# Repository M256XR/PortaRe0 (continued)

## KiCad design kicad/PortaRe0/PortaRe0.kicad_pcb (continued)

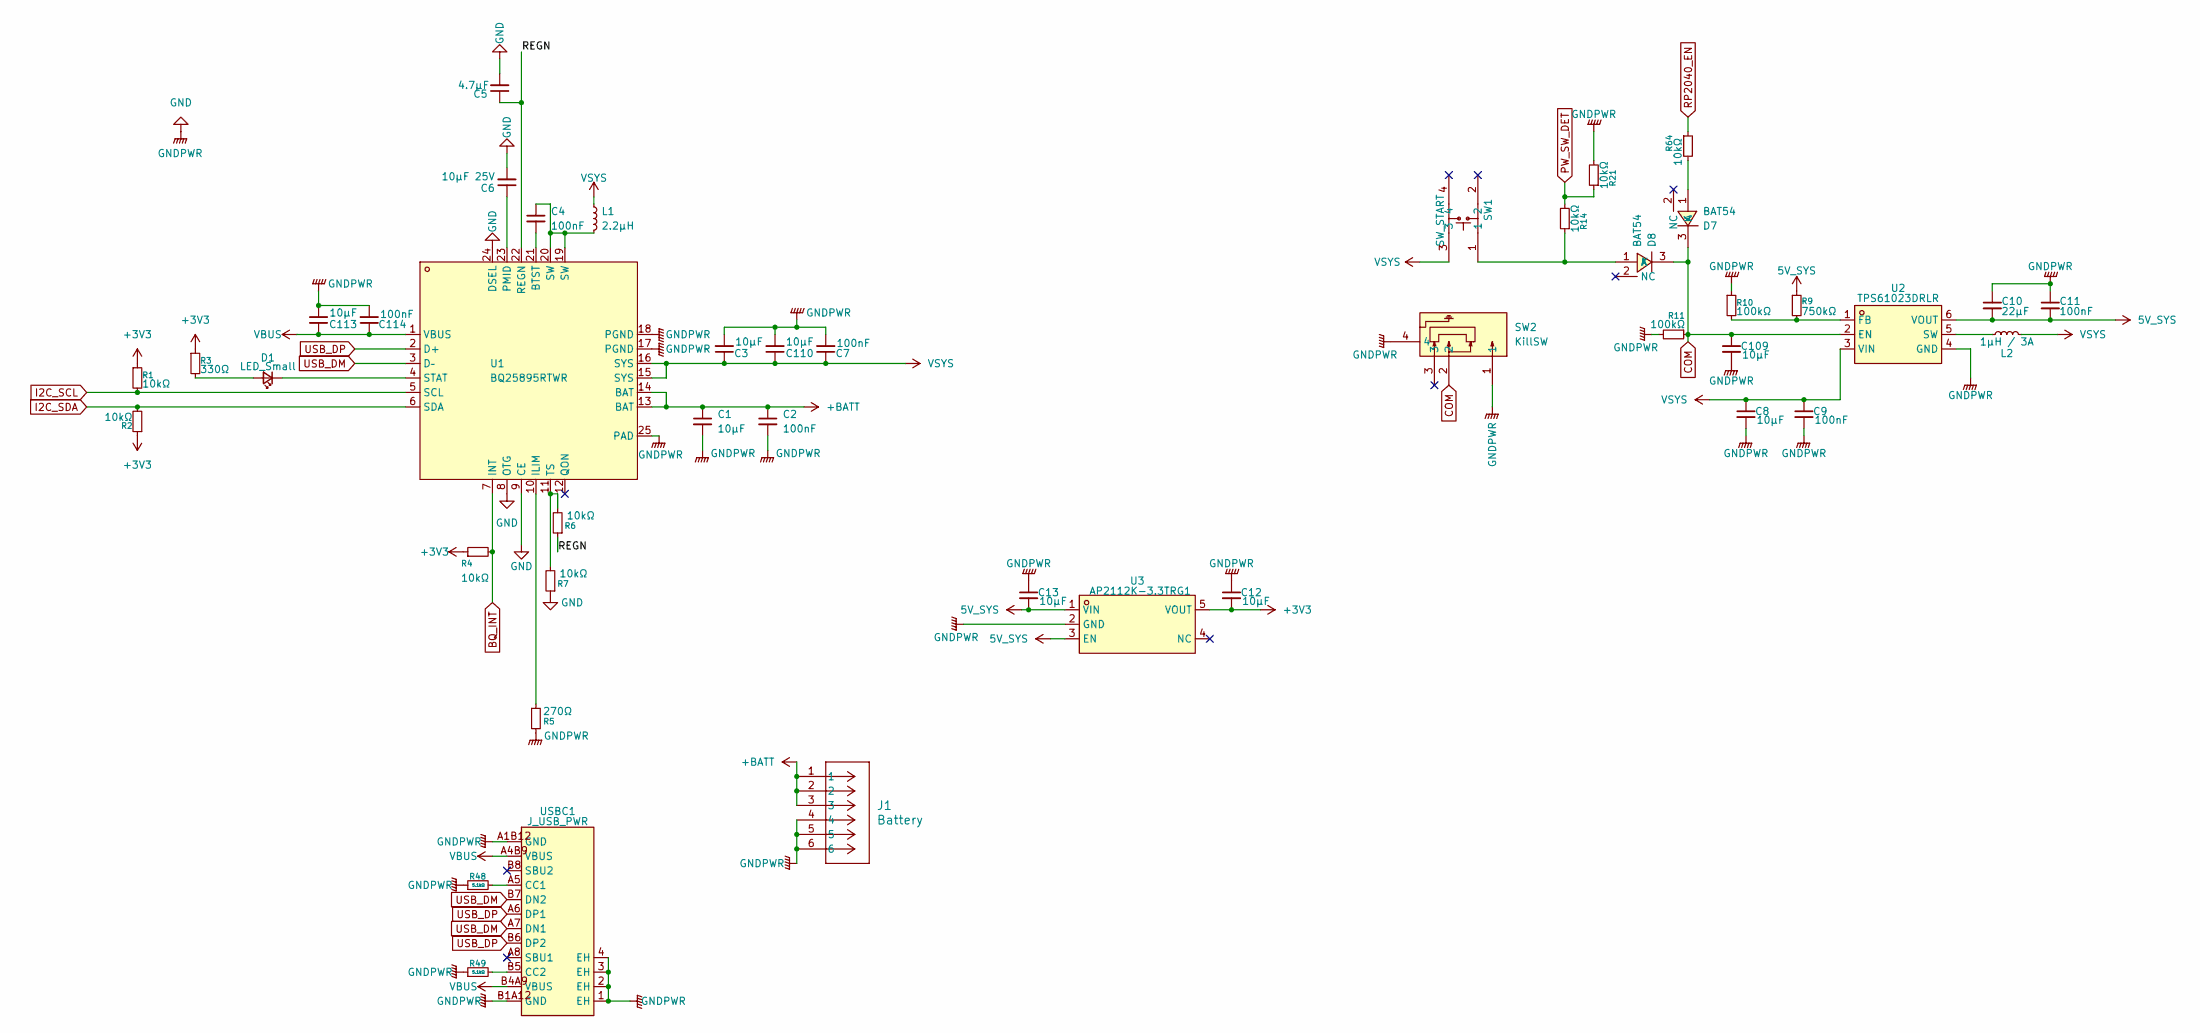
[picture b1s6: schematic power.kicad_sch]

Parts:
C1, C3, C8, C13, C109, C110, C113: 10μF; C_0603_1608Metric
C2, C4, C7, C9, C11, C114: 100nF; C_0402_1005Metric
C5: 4.7μF; C_0402_1005Metric
C6: 10μF 25V; C_0603_1608Metric
C10: 22μF; C_0603_1608Metric
C12: 10μF; C_0402_1005Metric
D1: LED_Small; LED_0603_1608Metric
D7, D8: BAT54; SOT-23-3_L2.9-W1.4-P1.90-LS2.6-BR; LCSC Part C466635
J1: Battery; CONN_BM06B-ACHFKS-GACN-ETF_JST
L1: 2.2μH; IND-SMD_L4.4-W4.2
L2: 1µH / 3A; IND-SMD_L3.2-W2.5_CKST322512-2.2UH
R1, R2, R4, R6, R7, R14, R21, R64: 10kΩ; R_0402_1005Metric
R3: 330Ω; R_0402_1005Metric
R5: 270Ω; R_0603_1608Metric
R9: 750kΩ; R_0603_1608Metric
R10, R11: 100kΩ; R_0402_1005Metric
R48, R49: 5.1kΩ; R_0402_1005Metric
SW1: SW_START; KEY-SMD_4P-SKSCLXX010; LCSC Part C115361
SW2: KillSW; SW-TH_MSK12C02; LCSC Part C431540
U1: BQ25895RTWR; QFN-24_L4.0-W4.0-P0.50-TL-EP2.7; LCSC Part C80200
U2: TPS61023DRLR; SOT-563_L1.6-W1.2-P0.50-LS1.6-BR; LCSC Part C919459
U3: AP2112K-3.3TRG1; SOT-25-5_L2.9-W1.6-P0.95-LS2.8-BL; LCSC Part C51118
USBC1: J_USB_PWR; USB-C_SMD-TYPE-C-31-M-12_1; LCSC Part C165948

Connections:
5V_SYS: C10.2, C11.2, C13.2, R9.1, U2.6 (VOUT), U3.1 (VIN), U3.3 (EN); also elsewhere on the board
+3V3: C12.2, R1.1, R2.1, R3.1, R4.1, U3.5 (VOUT); also elsewhere on the board
+BATT: C1.1, C2.1, J1.1, J1.2, J1.3, U1.13 (BAT), U1.14 (BAT)
/power/REGN: C5.1, R6.1, U1.22 (REGN)
BQ_INT: R4.2, U1.7 (INT); also elsewhere on the board
COM: C109.1, D7.3 (K), D8.3 (K), R11.1, SW2.2, U2.2 (EN)
GND: C1.2, C2.2, C3.2, C5.2, C6.2, C7.2, C8.2, C9.2, C10.1, C11.1, C12.1, C13.1, C109.2, C110.2, C113.2, C114.2, J1.4, J1.5, J1.6, R5.2, R7.1, R10.1, R11.2, R21.2, R48.1, R49.1, SW2.1, SW2.4, U1.8 (OTG), U1.9 (CE), U1.17 (PGND), U1.18 (PGND), U1.24 (DSEL), U1.25 (PAD), U2.4 (GND), U3.2 (GND), USBC1.1 (EH), USBC1.2 (EH), USBC1.3 (EH), USBC1.4 (EH), USBC1.A1B12 (GND), USBC1.B1A12 (GND); also elsewhere on the board
I2C_SCL: R1.2, U1.5 (SCL); also elsewhere on the board
I2C_SDA: R2.2, U1.6 (SDA); also elsewhere on the board
unnamed: C4.1, L1.2, U1.19 (SW), U1.20 (SW)
unnamed: D1.2 (A), R3.2
unnamed: D1.1 (K), U1.4 (STAT)
unnamed: D7.1 (A), R64.2
unnamed: D8.1 (A), R14.1, SW1.1
unnamed: C4.2, U1.21 (BTST)
unnamed: R5.1, U1.10 (ILIM)
unnamed: C6.1, U1.23 (PMID)
unnamed: R6.2, R7.2, U1.11 (TS)
unnamed: R9.2, R10.2, U2.1 (FB)
unnamed: L2.1, U2.5 (SW)
unnamed: R48.2, USBC1.A5 (CC1)
unnamed: R49.2, USBC1.B5 (CC2)
PW_SW_DET: R14.2, R21.1; also elsewhere on the board
RP2040_EN: R64.1; also elsewhere on the board
USB_DM: U1.3 (D–), USBC1.A7 (DN1), USBC1.B7 (DN2)
USB_DP: U1.2 (D+), USBC1.A6 (DP1), USBC1.B6 (DP2)
VBUS: C113.1, C114.1, U1.1 (VBUS), USBC1.A4B9 (VBUS), USBC1.B4A9 (VBUS)
VSYS: C3.1, C7.1, C8.1, C9.1, C110.1, L1.1, L2.2, SW1.3, U1.15 (SYS), U1.16 (SYS), U2.3 (VIN); also elsewhere on the board

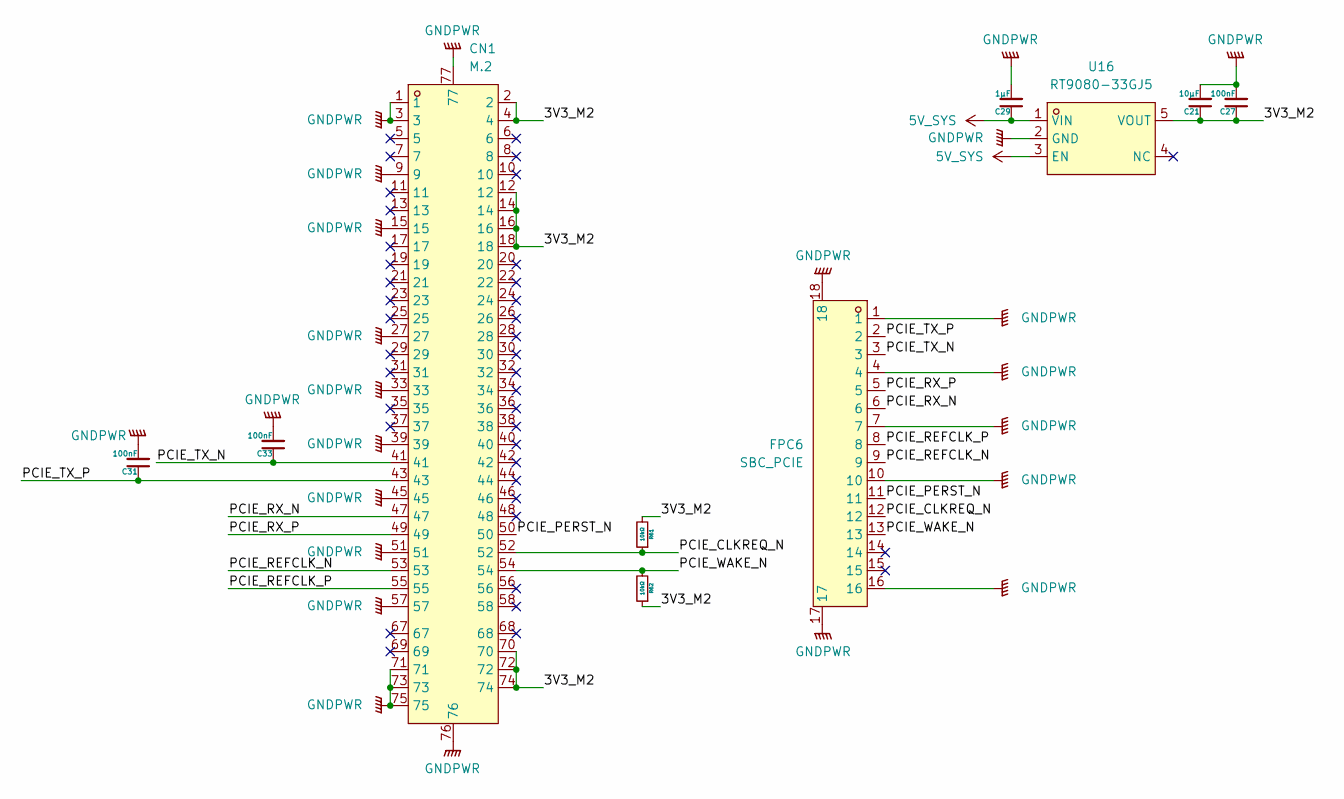
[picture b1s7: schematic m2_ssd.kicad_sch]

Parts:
C21: 10μF; C_0402_1005Metric
C27, C31, C33: 100nF; C_0402_1005Metric
C29: 1μF; C_0402_1005Metric
CN1: M.2; CONN-SMD_67P-P0.50-V_NXSM0-S67XX-XX40; LCSC Part C367029
FPC6: SBC_PCIE; FPC-SMD_16P-P0.50_FPC-05F-16PH20; LCSC Part C2856801
R61, R62: 10kΩ; R_0402_1005Metric
U16: RT9080-33GJ5; TSOT-23-5_L2.9-W1.6-P0.95-LS2.8-BL; LCSC Part C841192

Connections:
5V_SYS: C29.1, U16.1 (VIN), U16.3 (EN); also elsewhere on the board
/m2_ssd/3V3_M2: C21.1, C27.1, CN1.2, CN1.4, CN1.12, CN1.14, CN1.16, CN1.18, CN1.70, CN1.72, CN1.74, R61.2, R62.1, U16.5 (VOUT); also elsewhere on the board
/m2_ssd/PCIE_CLKREQ_N: CN1.52, FPC6.12, R61.1; also elsewhere on the board
/m2_ssd/PCIE_TX_N: C33.1, CN1.41, FPC6.3; also elsewhere on the board
/m2_ssd/PCIE_TX_P: C31.1, CN1.43, FPC6.2; also elsewhere on the board
/m2_ssd/PCIE_WAKE_N: CN1.54, FPC6.13, R62.2; also elsewhere on the board
GND: C21.2, C27.2, C29.2, C31.2, C33.2, CN1.1, CN1.3, CN1.9, CN1.15, CN1.27, CN1.33, CN1.39, CN1.45, CN1.51, CN1.57, CN1.71, CN1.73, CN1.75, CN1.76, CN1.77, FPC6.1, FPC6.4, FPC6.7, FPC6.10, FPC6.16, FPC6.17, FPC6.18, U16.2 (GND); also elsewhere on the board
unnamed: CN1.47, FPC6.6
unnamed: CN1.49, FPC6.5
unnamed: CN1.50, FPC6.11
unnamed: CN1.53, FPC6.9
unnamed: CN1.55, FPC6.8

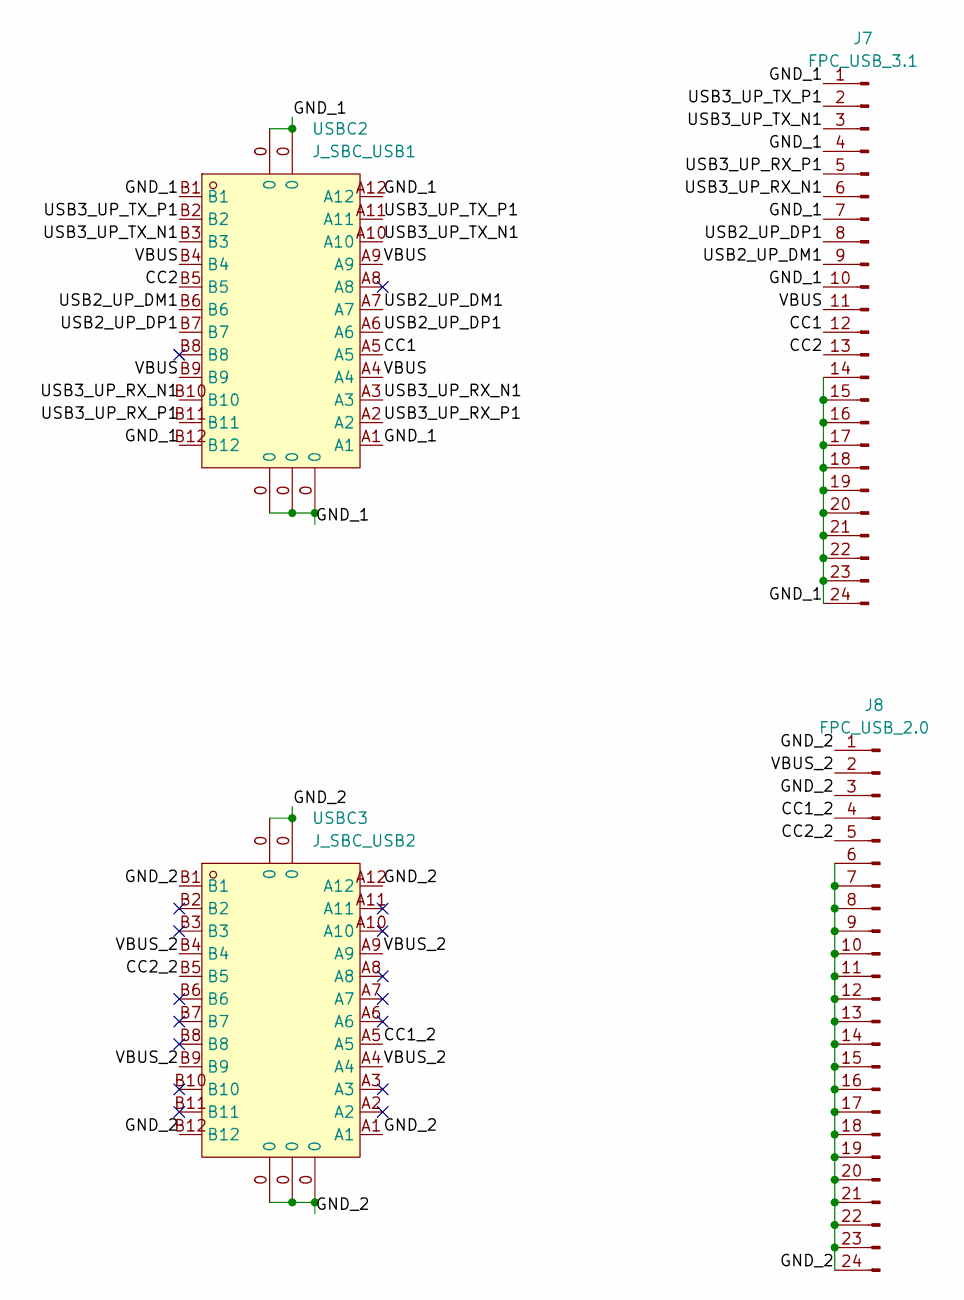
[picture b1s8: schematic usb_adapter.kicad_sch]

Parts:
J7: FPC_USB_3.1
J8: FPC_USB_2.0
USBC2: J_SBC_USB1; USB-C-SMD_TYPE-C-USB-3; LCSC Part C168690
USBC3: J_SBC_USB2; USB-C-SMD_TYPE-C-USB-3; LCSC Part C168690

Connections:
unnamed: J7.1, J7.4, J7.7, J7.10, J7.14, J7.15, J7.16, J7.17, J7.18, J7.19, J7.20, J7.21, J7.22, J7.23, J7.24, USBC2.0, USBC2.A1, USBC2.A12, USBC2.B1, USBC2.B12
unnamed: J7.2, USBC2.A11, USBC2.B2
unnamed: J7.3, USBC2.A10, USBC2.B3
unnamed: J7.5, USBC2.A2, USBC2.B11
unnamed: J7.6, USBC2.A3, USBC2.B10
unnamed: J7.8, USBC2.A6, USBC2.B7
unnamed: J7.9, USBC2.A7, USBC2.B6
unnamed: J7.11, USBC2.A4, USBC2.A9, USBC2.B4, USBC2.B9
unnamed: J7.12, USBC2.A5
unnamed: J7.13, USBC2.B5
unnamed: J8.1, J8.3, J8.6, J8.7, J8.8, J8.9, J8.10, J8.11, J8.12, J8.13, J8.14, J8.15, J8.16, J8.17, J8.18, J8.19, J8.20, J8.21, J8.22, J8.23, J8.24, USBC3.0, USBC3.A1, USBC3.A12, USBC3.B1, USBC3.B12
unnamed: J8.2, USBC3.A4, USBC3.A9, USBC3.B4, USBC3.B9
unnamed: J8.4, USBC3.A5
unnamed: J8.5, USBC3.B5

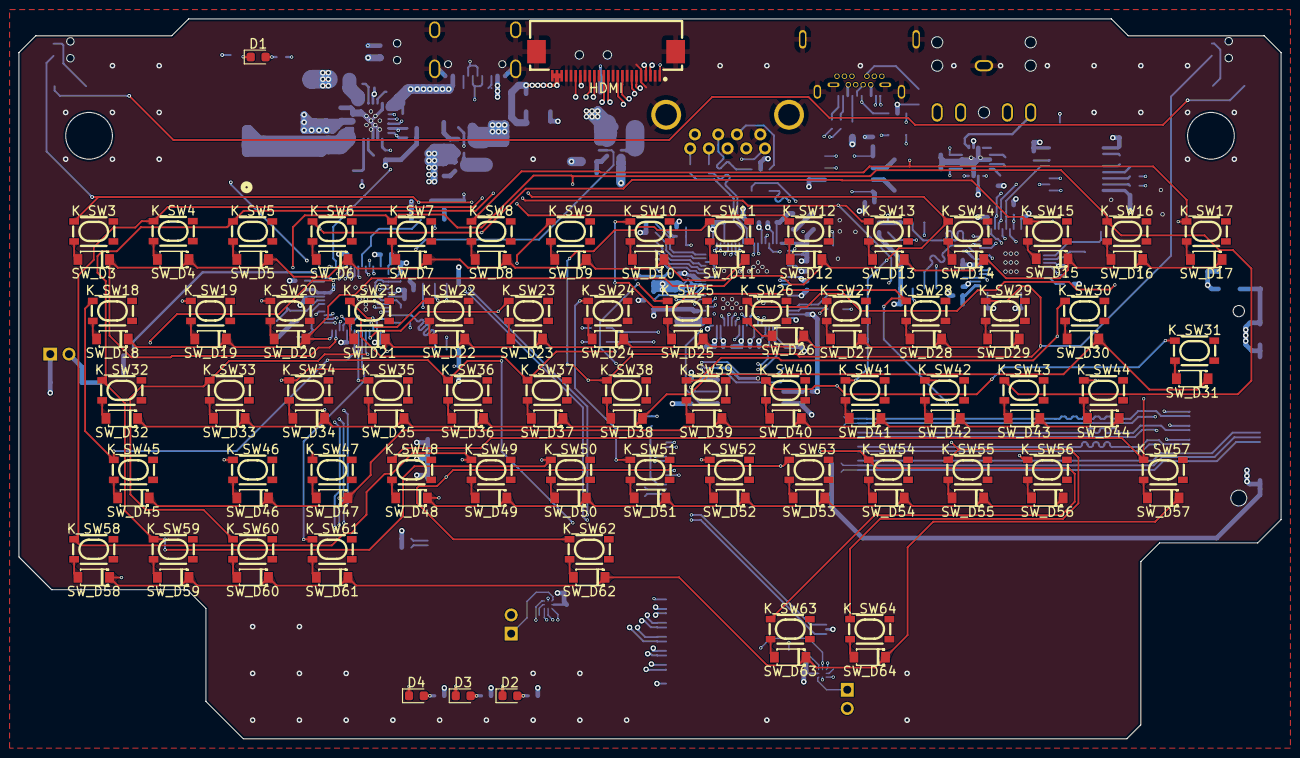
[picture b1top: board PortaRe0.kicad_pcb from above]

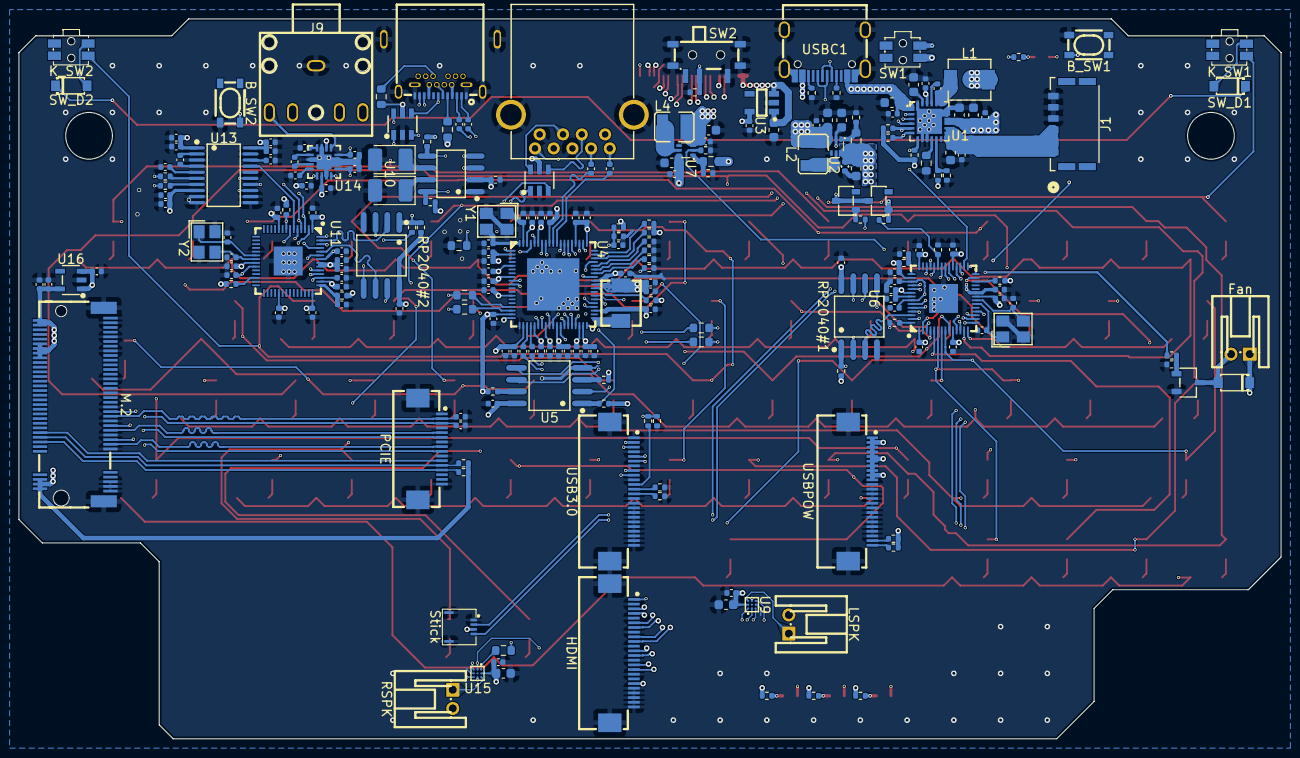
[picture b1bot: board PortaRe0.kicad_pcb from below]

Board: 6 copper layers, 135.0 x 77.0 mm, 357 parts (228 on the bottom side), 266 nets.

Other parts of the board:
Fan: Fan; CONN-TH_S2B-PH-K-S-LF-SN
HDMI: J_HDMI_CTRL; FPC-SMD_24P-P0.50_FPC-05F-24PH20
HDMI#2: J_SBC_HDMI; FPC-SMD_24P-P0.50_FPC-05F-24PH20
LSPK: SPK_L; CONN-TH_S2B-PH-K-S-LF-SN
M.2: M.2; CONN-SMD_67P-P0.50-V_NXSM0-S67XX-XX40
PCIE: SBC_PCIE; FPC-SMD_16P-P0.50_FPC-05F-16PH20
RSPK: SPK_R; CONN-TH_S2B-PH-K-S-LF-SN
Stick: 5034800440; FPC-SMD_5034800400
USB3.0: J_SBC_USB_3.1; FPC-SMD_24P-P0.50_FPC-05F-24PH20
USBPOW: J_SBC_USB_2.0; FPC-SMD_24P-P0.50_FPC-05F-24PH20

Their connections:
5V_SYS: Fan.1, HDMI.18, HDMI.22, HDMI.23, HDMI.24, USBPOW.1, USBPOW.2, USBPOW.3, USBPOW.4, USBPOW.5, USBPOW.6, USBPOW.7, USBPOW.8, USBPOW.9, USBPOW.10; also elsewhere on the board
+3V3: Stick.3; also elsewhere on the board
/Connectors/HDMI_CEC: HDMI.19, HDMI#2.19
/Connectors/HDMI_CLKN: HDMI.13, HDMI#2.13
/Connectors/HDMI_CLKP: HDMI.12, HDMI#2.12
/Connectors/HDMI_D0N: HDMI.10, HDMI#2.10
/Connectors/HDMI_D0P: HDMI.9, HDMI#2.9
/Connectors/HDMI_D1N: HDMI.7, HDMI#2.7
/Connectors/HDMI_D1P: HDMI.6, HDMI#2.6
/Connectors/HDMI_D2N: HDMI.4, HDMI#2.4
/Connectors/HDMI_D2P: HDMI.3, HDMI#2.3
/Connectors/HDMI_HPD: HDMI.1, HDMI#2.1
/Connectors/HDMI_SCL: HDMI.15, HDMI#2.15
/Connectors/HDMI_SDA: HDMI.16, HDMI#2.16
/audio/SPK_L+: LSPK.1; also elsewhere on the board
/audio/SPK_L-: LSPK.2; also elsewhere on the board
/audio/SPK_R+: RSPK.1; also elsewhere on the board
/audio/SPK_R-: RSPK.2; also elsewhere on the board
/m2_ssd/3V3_M2: M.2.2, M.2.4, M.2.12, M.2.14, M.2.16, M.2.18, M.2.70, M.2.72, M.2.74; also elsewhere on the board
/m2_ssd/PCIE_CLKREQ_N: M.2.52, PCIE.12; also elsewhere on the board
/m2_ssd/PCIE_PERST_N: M.2.50, PCIE.11
/m2_ssd/PCIE_REFCLK_N: M.2.53, PCIE.9
/m2_ssd/PCIE_REFCLK_P: M.2.55, PCIE.8
/m2_ssd/PCIE_RX_N: M.2.47, PCIE.6
/m2_ssd/PCIE_RX_P: M.2.49, PCIE.5
/m2_ssd/PCIE_TX_N: M.2.41, PCIE.3; also elsewhere on the board
/m2_ssd/PCIE_TX_P: M.2.43, PCIE.2; also elsewhere on the board
/m2_ssd/PCIE_WAKE_N: M.2.54, PCIE.13; also elsewhere on the board
GND: HDMI.2, HDMI.5, HDMI.8, HDMI.11, HDMI.14, HDMI.17, HDMI.20, HDMI.21, HDMI.25, HDMI.26, HDMI#2.2, HDMI#2.5, HDMI#2.8, HDMI#2.11, HDMI#2.14, HDMI#2.17, HDMI#2.20, HDMI#2.21, HDMI#2.22, HDMI#2.23, HDMI#2.24, HDMI#2.25, HDMI#2.26, M.2.1, M.2.3, M.2.9, M.2.15, M.2.27, M.2.33, M.2.39, M.2.45, M.2.51, M.2.57, M.2.71, M.2.73, M.2.75, M.2.76, M.2.77, PCIE.1, PCIE.4, PCIE.7, PCIE.10, PCIE.16, PCIE.17, PCIE.18, Stick.1, Stick.5, Stick.6, USB3.0.1, USB3.0.4, USB3.0.7, USB3.0.10, USB3.0.14, USB3.0.15, USB3.0.16, USB3.0.17, USB3.0.18, USB3.0.19, USB3.0.20, USB3.0.21, USB3.0.22, USB3.0.23, USB3.0.24, USB3.0.25, USB3.0.26, USBPOW.11, USBPOW.12, USBPOW.13, USBPOW.14, USBPOW.15, USBPOW.16, USBPOW.17, USBPOW.18, USBPOW.19, USBPOW.20, USBPOW.21, USBPOW.22, USBPOW.25, USBPOW.26; also elsewhere on the board
unnamed 109: Fan.2; also elsewhere on the board
unnamed 136: USBPOW.23; also elsewhere on the board
unnamed 137: USBPOW.24; also elsewhere on the board
unnamed 138: USB3.0.12; also elsewhere on the board
unnamed 139: USB3.0.13; also elsewhere on the board
STICK_X: Stick.2; also elsewhere on the board
STICK_Y: Stick.4; also elsewhere on the board
USB2_UP_DM: USB3.0.9; also elsewhere on the board
USB2_UP_DP: USB3.0.8; also elsewhere on the board
USB2_UP_VBUS: USB3.0.11; also elsewhere on the board
USB3_UP_RX_N: USB3.0.6; also elsewhere on the board
USB3_UP_RX_P: USB3.0.5; also elsewhere on the board
USB3_UP_TX_N: USB3.0.3; also elsewhere on the board
USB3_UP_TX_P: USB3.0.2; also elsewhere on the board

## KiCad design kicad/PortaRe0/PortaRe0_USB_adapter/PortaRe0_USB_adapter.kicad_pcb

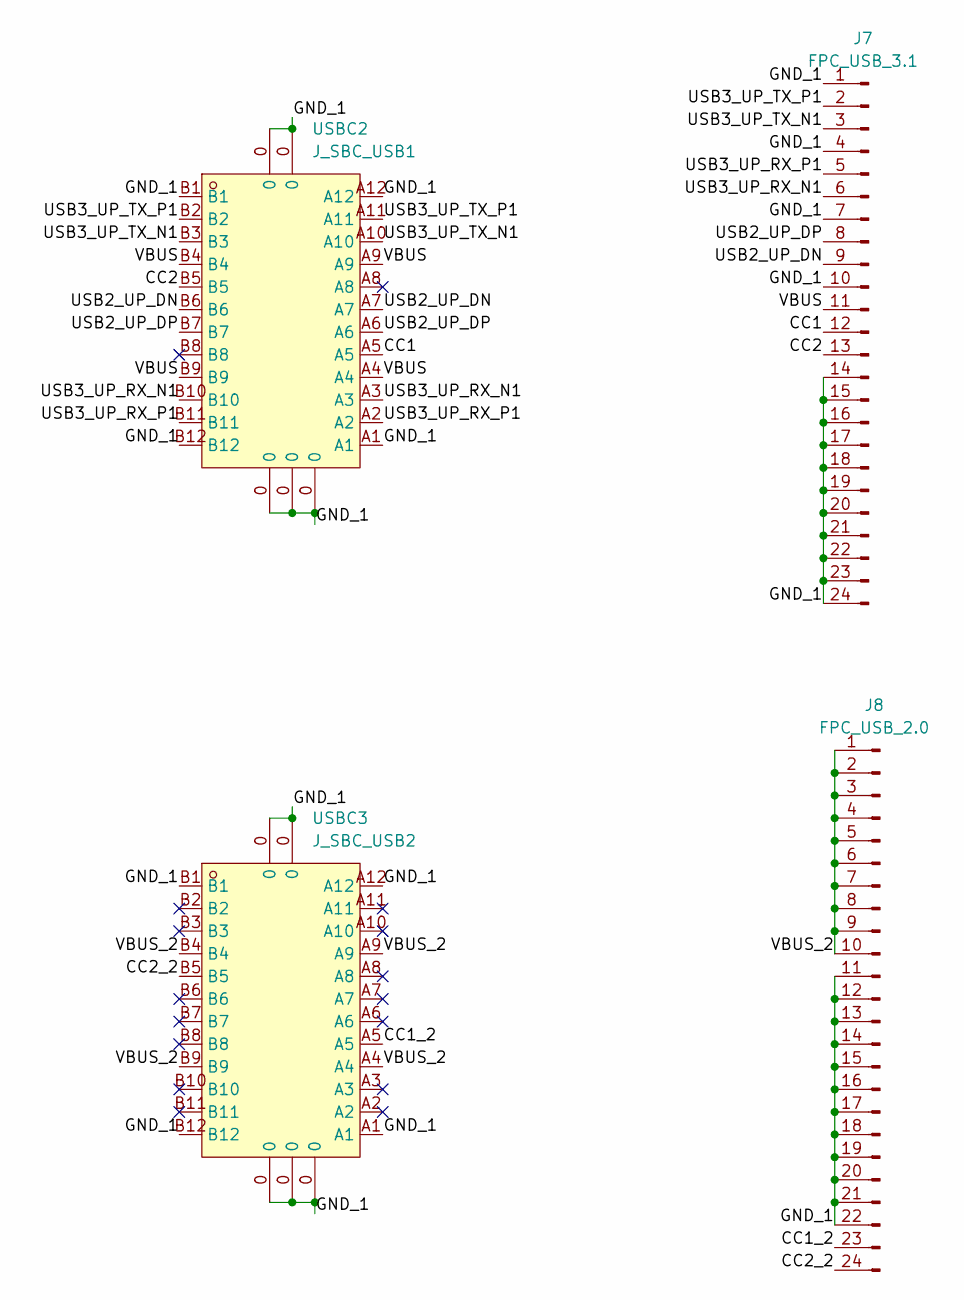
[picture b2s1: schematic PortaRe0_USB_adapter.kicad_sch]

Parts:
J7: FPC_USB_3.1; FPC-24P-0.5mm
J8: FPC_USB_2.0; FPC-24P-0.5mm
USBC2: J_SBC_USB1; USB-C-SMD_TYPE-C-USB-3; LCSC Part C168690
USBC3: J_SBC_USB2; USB-C-SMD_TYPE-C-USB-3; LCSC Part C168690

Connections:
/CC1: J7.12, USBC2.A5
/CC1_2: J8.23, USBC3.A5
/CC2: J7.13, USBC2.B5
/CC2_2: J8.24, USBC3.B5
/GND_1: J7.1, J7.4, J7.7, J7.10, J7.14, J7.15, J7.16, J7.17, J7.18, J7.19, J7.20, J7.21, J7.22, J7.23, J7.24, J8.11, J8.12, J8.13, J8.14, J8.15, J8.16, J8.17, J8.18, J8.19, J8.20, J8.21, J8.22, USBC2.0, USBC2.A1, USBC2.A12, USBC2.B1, USBC2.B12, USBC3.0, USBC3.A1, USBC3.A12, USBC3.B1, USBC3.B12
/USB2_UP_DN: J7.9, USBC2.A7, USBC2.B6
/USB2_UP_DP: J7.8, USBC2.A6, USBC2.B7
/USB3_UP_RX_N1: J7.6, USBC2.A3, USBC2.B10
/USB3_UP_RX_P1: J7.5, USBC2.A2, USBC2.B11
/USB3_UP_TX_N1: J7.3, USBC2.A10, USBC2.B3
/USB3_UP_TX_P1: J7.2, USBC2.A11, USBC2.B2
/VBUS: J7.11, USBC2.A4, USBC2.A9, USBC2.B4, USBC2.B9
/VBUS_2: J8.1, J8.2, J8.3, J8.4, J8.5, J8.6, J8.7, J8.8, J8.9, J8.10, USBC3.A4, USBC3.A9, USBC3.B4, USBC3.B9

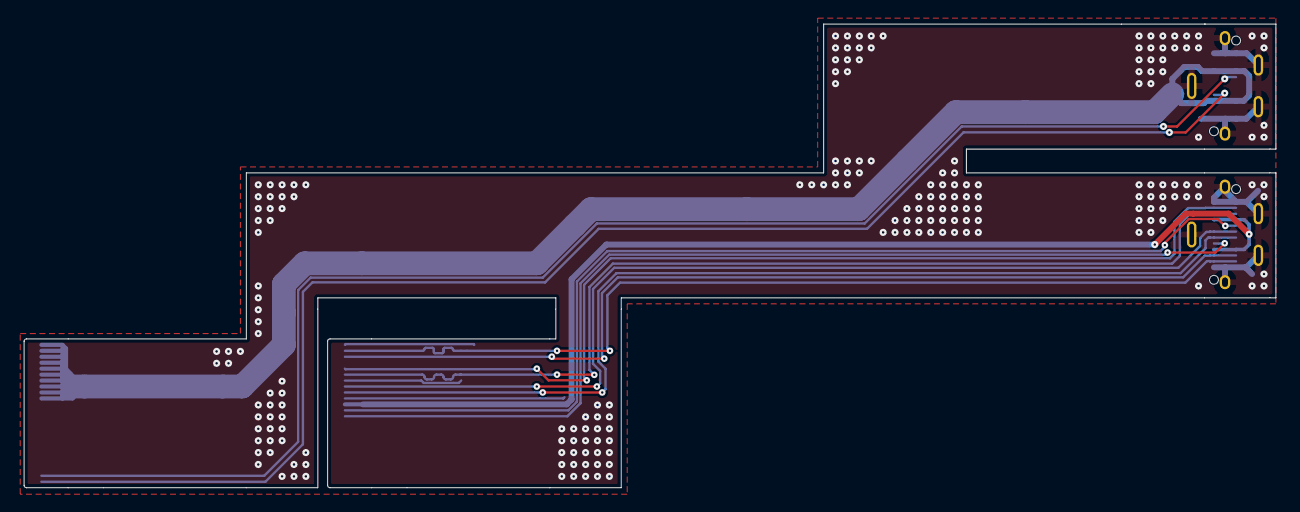
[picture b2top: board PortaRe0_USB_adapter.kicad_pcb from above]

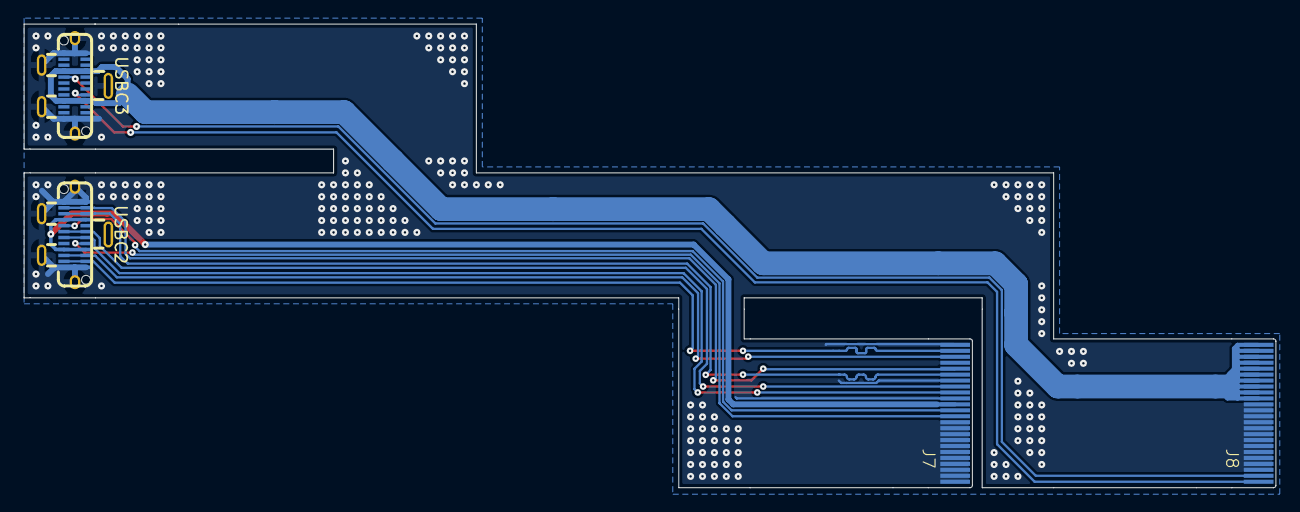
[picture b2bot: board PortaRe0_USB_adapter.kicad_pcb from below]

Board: 2 copper layers, 105.2 x 39.0 mm, 4 parts (4 on the bottom side), 13 nets.

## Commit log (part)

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2026-02-19 Initial commit: add project structure and BOM
2026-02-19 Add KiCad project
2026-02-19 Add KiCad component libraries
2026-02-22 Docs: session13終了処理・PROGRESS/index更新・launch_claude追加
2026-02-22 Docs: 終了処理にgit pushを追加
2026-02-22 Docs: chat_logs/原文/移行・CONTEXT/PROJECT_PLAN更新・Session原文追加
2026-02-23 Docs: session16終了処理・PROGRESS/index更新・powerシート完成
2026-02-25 Fix: connectorsシートファイル名大文字C統一（Linux case-sensitive対応）
2026-03-04 Docs: session32終了処理・ドキュメント構成整理・session_close.py作成
2026-03-04 Docs: README フェーズ更新（Phase 3 PCBレイアウト進行中）
2026-03-05 Docs: session33終了処理・J4コネクタ確定・pcb_layout_notes作成
2026-03-05 Docs: specs/index.md にバッテリーコネクタ追記（BM06B-ACHFKS-GACN-ETF）
2026-03-07 Docs: session34終了処理・0402化確定・ディスプレイ調査・PCBレイアウト進行中
2026-03-07 Docs: session34ログ完全版をSession35に保存・index.md更新
2026-03-07 Docs: session34ログ整理（途中抽出削除・完全版をSession34に統一）
2026-03-08 Docs: session35終了処理・TPS61023 FB接続ミス確認・M.2クリアランス1.1mm
2026-03-09 Docs: session36終了処理・VL812受動部品配置方針確定
2026-03-11 Docs: session37終了処理・部品配置完了・ルーティング開始・FPC給電ピン修正
2026-03-14 Docs: session38終了処理・ルーティング大幅進捗（電源幹線〜USB差動ペア完了）
2026-03-15 Docs: session39終了処理・MAX98357A I2S・BOOTSEL・M.2 PCIe配線完了
2026-03-17 Docs: session40終了処理・メインPCB完了・hdmi_adapter/usb_adapter(FPC)完了・software/フォルダ作成
2026-03-17 Software: session01終了処理・フレームワーク選定・Windows ARM EDK2計画
2026-03-20 Docs: session02終了処理・EDK2 ArmConfigureMmuクラッシュ絞り込み・PROGRESS/index更新
2026-03-23 Docs: Session41終了処理・PROGRESS/index/README更新・ガーバー・CPL追加
2026-03-23 Software: migrate agent docs and update debug SD boot flow
2026-03-23 Software: add external EFI boot probe
2026-03-23 Software: log direct EFI load failures
2026-03-23 Software: refresh sd image before raw write
2026-03-23 Software: allow external EFI images on A733
